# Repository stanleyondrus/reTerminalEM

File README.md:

# reTerminalEM

reTerminalEM is an open-source expansion module platform for reTerminal's high speed interface

#### More information: https://stanleyprojects.com/projects/reterminal_module/

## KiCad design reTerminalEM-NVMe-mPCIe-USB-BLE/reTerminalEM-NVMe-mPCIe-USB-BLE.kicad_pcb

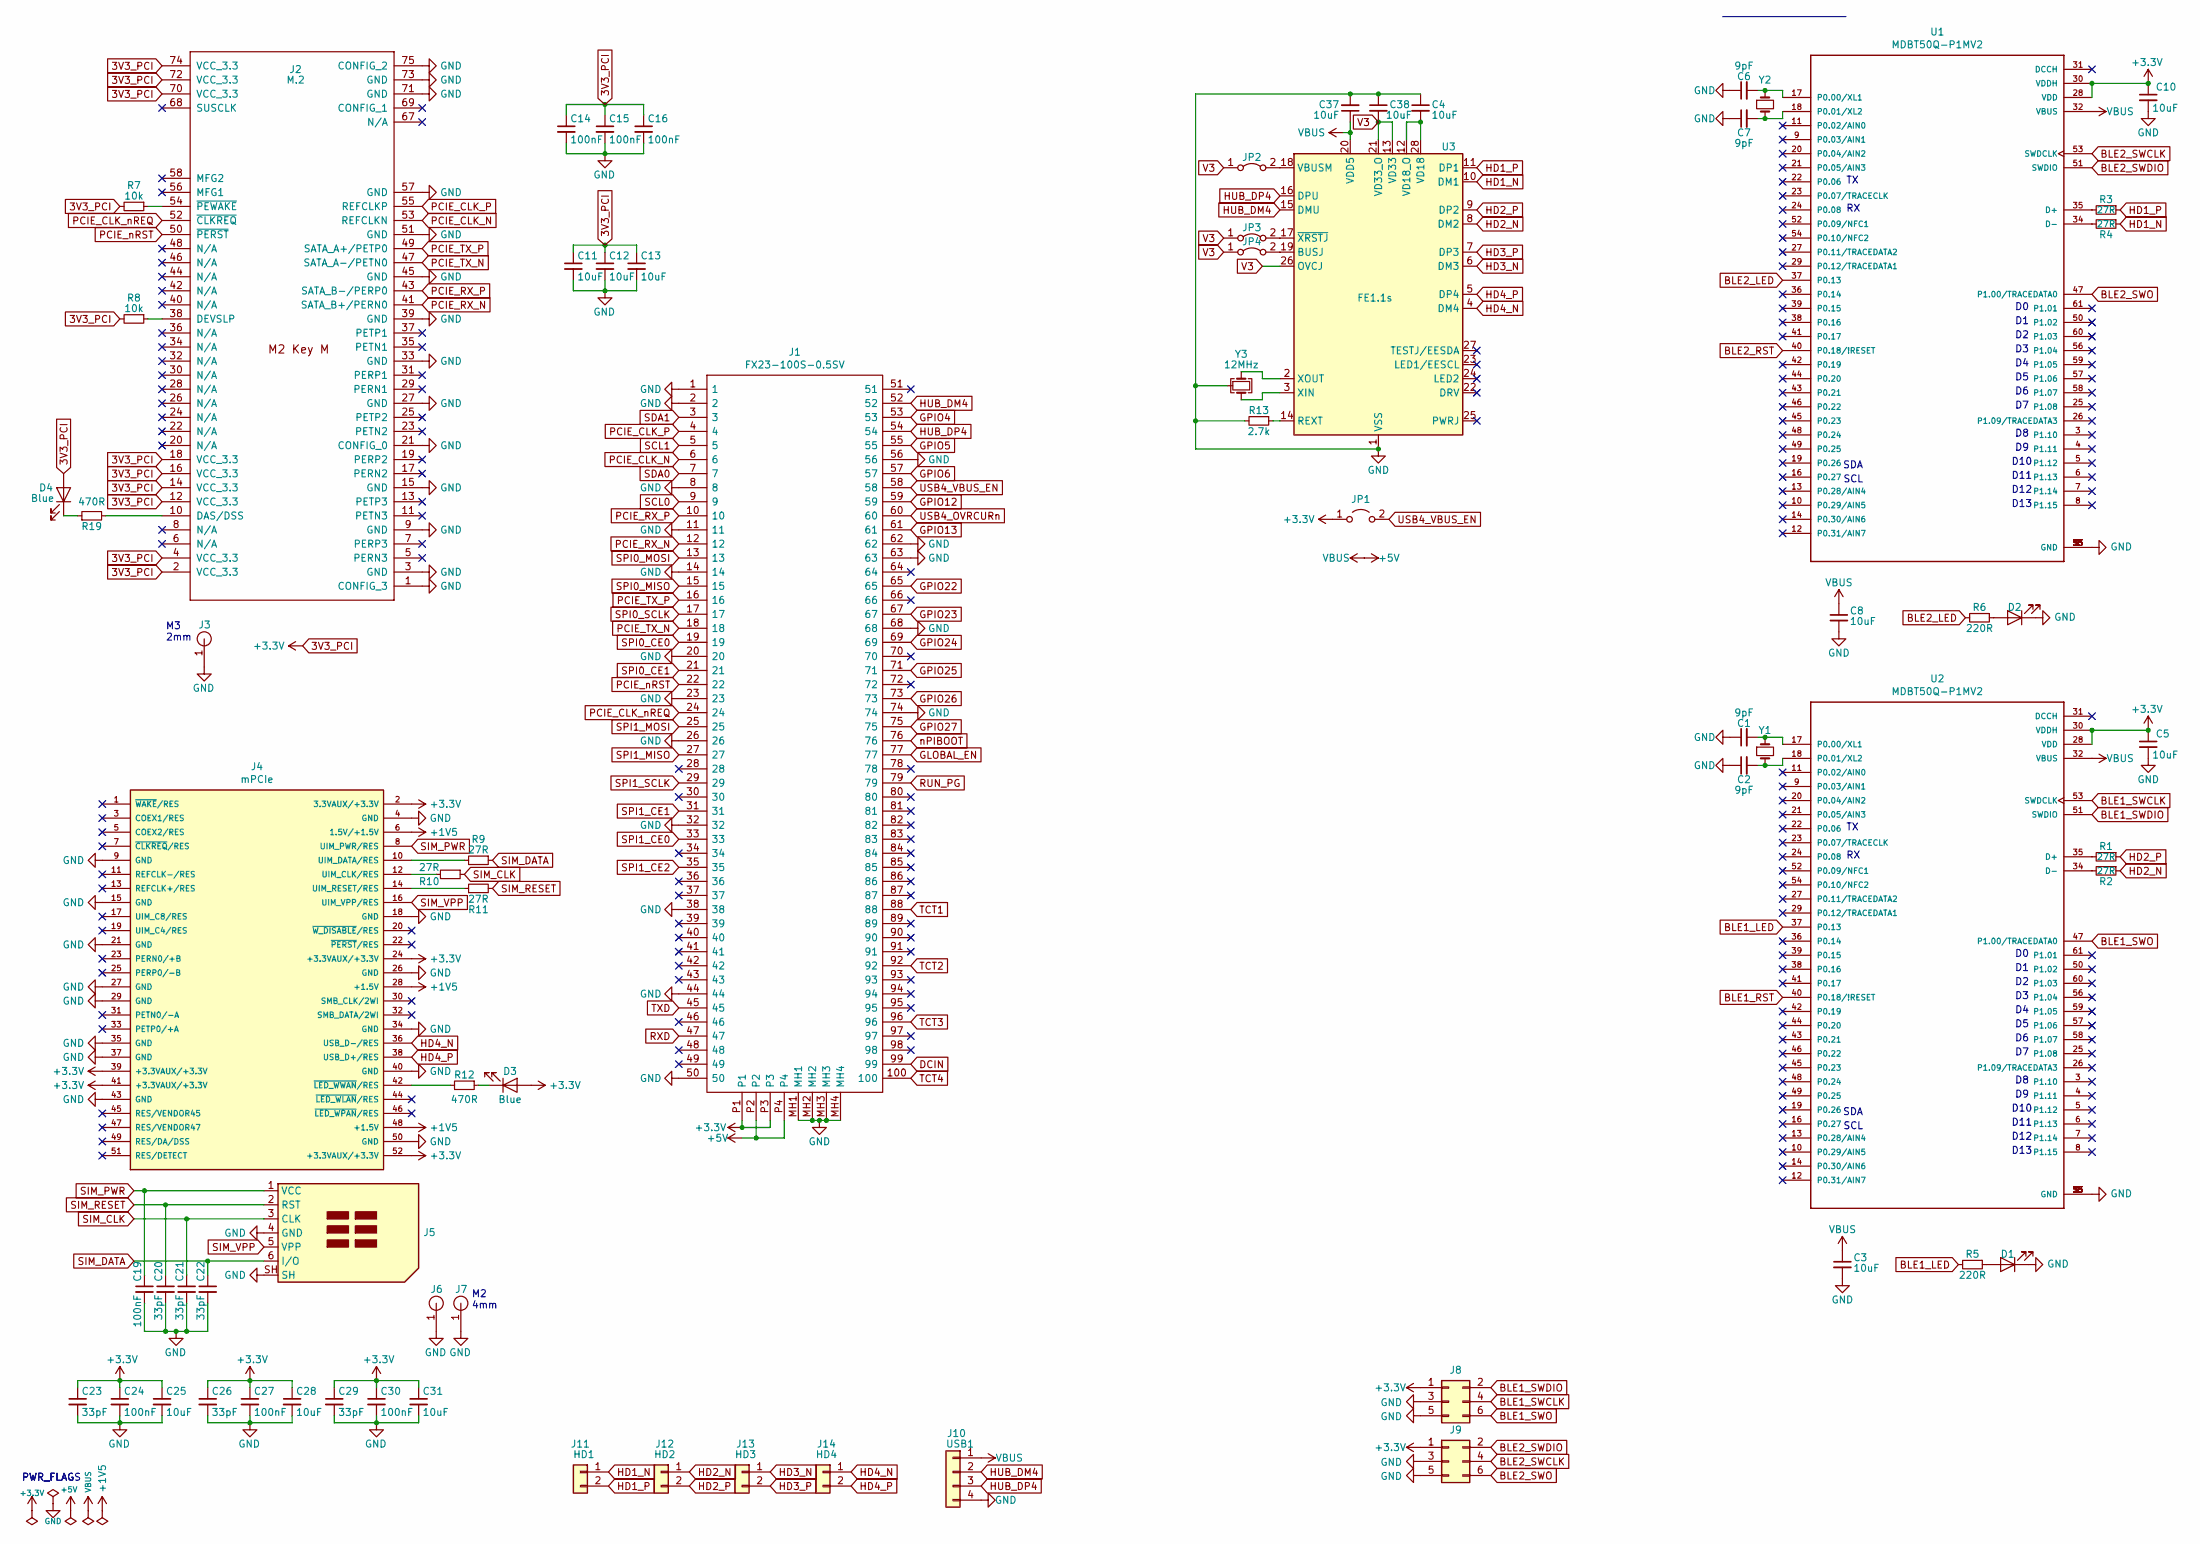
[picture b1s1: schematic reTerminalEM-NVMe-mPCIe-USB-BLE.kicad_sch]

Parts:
C1, C2, C6, C7: 9pF; C_0402_1005Metric; MPN CBR04C909B1GAC
C3, C5, C8, C10: 10uF; C_0402_1005Metric; MPN LDK105CBJ106MVLF
C4, C11, C12, C13, C25, C28, C31, C37, C38: 10uF; C_0805_2012Metric; MPN CL21A106KAYNNNE
C14, C15, C16, C19, C24, C27, C30: 100nF; C_0402_1005Metric; MPN CC0402KRX7R7BB104
C20, C21, C22, C23, C26, C29: 33pF; C_0402_1005Metric; MPN CC0402JRNPO9BN330
D1, D2: R; LED_0402_1005Metric; MPN NCD0402R1
D3, D4: Blue; LED_0402_1005Metric; MPN NCD0402B1
J1: FX23-100S-0.5SV; MPN FX23-100S-0.5SV
J2: M.2; TE_1-2199230-5; MPN 1-2199230-5
J3: J_Standoff_M3_H2.5; WE_WA-SMSI_9774025360; MPN 9774020360R
J4: mPCIe; TE_20412621; MPN 2041262-1
J5: J_SIM_Card_Nano_6P_Shielded; Molex_104224-0820; MPN 104224-0820
J6, J7: J_Standoff_M2_H4; WE_WA-SMSI_9774040243; MPN 9774040243R
J8, J9: Conn_02x03_Odd_Even; Tag-Connect_TC2030-IDC-NL_2x03_P1.27mm_Vertical
J10: USB1; PinSocket_1x04_P2.54mm_Vertical
J11: HD1; PinSocket_1x02_P2.54mm_Vertical
J12: HD2; PinSocket_1x02_P2.54mm_Vertical
J13: HD3; PinSocket_1x02_P2.54mm_Vertical
J14: HD4; PinSocket_1x02_P2.54mm_Vertical
JP1: Jumper_2_Open; SolderJumper-2_P1.3mm_Open_RoundedPad1.0x1.5mm
JP2, JP3, JP4: Jumper_2_Closed; SolderJumper-2_P1.3mm_Bridged_RoundedPad1.0x1.5mm
R1, R2, R3, R4, R9, R10, R11: 27R; R_0402_1005Metric; MPN RC0402JR-0727RL
R5, R6: 220R; R_0402_1005Metric; MPN 0402WGF2200TCE
R7, R8: 10k; R_0402_1005Metric; MPN RC0402FR-0710KL
R12, R19: 470R; R_0402_1005Metric; MPN RC0402FR-07470RL
R13: 2.7k; R_0402_1005Metric; MPN RC0402FR-072K7L
U1, U2: MDBT50Q-P1MV2; MPN MDBT50Q-P1MV2
U3: FE1.1s; SSOP-28_3.9x9.9mm_P0.635mm
Y1, Y2: 32.768kHz; Y_3215-2Pin_3.2x1.5mm; MPN FC-135 32.7680KA-AG3
Y3: 12MHz; Crystal_SMD_3225-4Pin_3.2x2.5mm; MPN 403WF12012IMR

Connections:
3V3_PCI: C5.1, C10.1, C11.1, C12.1, C13.1, C14.1, C15.1, C16.1, C23.1, C24.1, C25.1, C26.1, C27.1, C28.1, C29.1, C30.1, C31.1, D3.2 (A), D4.2 (A), J1.P1, J1.P3, J2.2 (VCC_3.3), J2.4 (VCC_3.3), J2.12 (VCC_3.3), J2.14 (VCC_3.3), J2.16 (VCC_3.3), J2.18 (VCC_3.3), J2.70 (VCC_3.3), J2.72 (VCC_3.3), J2.74 (VCC_3.3), J4.2 (3.3VAUX/+3.3V), J4.24 (+3.3VAUX/+3.3V), J4.39 (+3.3VAUX/+3.3V), J4.41 (+3.3VAUX/+3.3V), J4.52 (+3.3VAUX/+3.3V), J8.1, J9.1, JP1.1 (A), R7.2, R8.2, U1.28 (VDD), U1.30 (VDDH), U2.28 (VDD), U2.30 (VDDH)
+1V5: J4.6 (1.5V/+1.5V), J4.28 (+1.5V), J4.48 (+1.5V)
+5V: C3.1, C8.1, C37.1, J1.P2, J1.P4, J10.1, U1.32 (VBUS), U2.32 (VBUS), U3.20 (VDD5)
BLE1_LED: R5.2, U2.37 (P0.13)
BLE1_RST: U2.40 (P0.18/!RESET)
BLE1_SWCLK: J8.4, U2.53 (SWDCLK)
BLE1_SWDIO: J8.2, U2.51 (SWDIO)
BLE1_SWO: J8.6, U2.47 (P1.00/TRACEDATA0)
BLE2_LED: R6.2, U1.37 (P0.13)
BLE2_RST: U1.40 (P0.18/!RESET)
BLE2_SWCLK: J9.4, U1.53 (SWDCLK)
BLE2_SWDIO: J9.2, U1.51 (SWDIO)
BLE2_SWO: J9.6, U1.47 (P1.00/TRACEDATA0)
DCIN: J1.99
GLOBAL_EN: J1.77
GND: C1.1, C2.1, C3.2, C4.1, C5.2, C6.1, C7.1, C8.2, C10.2, C11.2, C12.2, C13.2, C14.2, C15.2, C16.2, C19.2, C20.2, C21.2, C22.2, C23.2, C24.2, C25.2, C26.2, C27.2, C28.2, C29.2, C30.2, C31.2, C37.2, C38.1, D1.1 (K), D2.1 (K), J1.1, J1.2, J1.8, J1.11, J1.14, J1.20, J1.23, J1.26, J1.32, J1.38, J1.44, J1.50, J1.56, J1.62, J1.63, J1.68, J1.74, J1.MH1, J1.MH2, J1.MH3, J1.MH4, J2.1 (CONFIG_3), J2.3 (GND), J2.9 (GND), J2.15 (GND), J2.21 (CONFIG_0), J2.27 (GND), J2.33 (GND), J2.39 (GND), J2.45 (GND), J2.51 (GND), J2.57 (GND), J2.71 (GND), J2.73 (GND), J2.75 (CONFIG_2), J2.S1 (GND), J2.S2 (GND), J3.1, J4.4 (GND), J4.9 (GND), J4.15 (GND), J4.18 (GND), J4.21 (GND), J4.26 (GND), J4.27 (GND), J4.29 (GND), J4.34 (GND), J4.35 (GND), J4.37 (GND), J4.40 (GND), J4.43 (GND), J4.50 (GND), J5.4 (GND), J5.SH, J6.1, J7.1, J8.3, J8.5, J9.3, J9.5, J10.4, R13.2, U1.1 (GND), U1.2 (GND), U1.15 (GND), U1.33 (GND), U1.55 (GND), U2.1 (GND), U2.2 (GND), U2.15 (GND), U2.33 (GND), U2.55 (GND), U3.1 (VSS), Y3.2, Y3.4
GPIO4: J1.53
GPIO5: J1.55
GPIO6: J1.57
GPIO12: J1.59
GPIO13: J1.61
GPIO22: J1.65
GPIO23: J1.67
GPIO24: J1.69
GPIO25: J1.71
GPIO26: J1.73
GPIO27: J1.75
HD1_N: J11.1, R4.1, U3.10 (DM1)
HD1_P: J11.2, R3.1, U3.11 (DP1)
HD2_N: J12.1, R2.1, U3.8 (DM2)
HD2_P: J12.2, R1.1, U3.9 (DP2)
HD3_N: J13.1, U3.6 (DM3)
HD3_P: J13.2, U3.7 (DP3)
HD4_N: J4.36 (USB_D-/RES), J14.1, U3.4 (DM4)
HD4_P: J4.38 (USB_D+/RES), J14.2, U3.5 (DP4)
HUB_DM4: J1.52, J10.2, U3.15 (DMU)
HUB_DP4: J1.54, J10.3, U3.16 (DPU)
unnamed: C1.2, U2.17 (P0.00/XL1), Y1.1
unnamed: C2.2, U2.18 (P0.01/XL2), Y1.2
unnamed: C4.2, U3.12 (VD18_O), U3.28 (VD18)
unnamed: C6.2, U1.17 (P0.00/XL1), Y2.1
unnamed: C7.2, U1.18 (P0.01/XL2), Y2.2
unnamed: D1.2 (A), R5.1
unnamed: D2.2 (A), R6.1
unnamed: D3.1 (K), R12.1
unnamed: D4.1 (K), R19.1
unnamed: J2.10 (DAS/DSS), R19.2
unnamed: J2.38 (DEVSLP), R8.1
unnamed: J2.54 (~PEWAKE), R7.1
unnamed: J4.10 (UIM_DATA/RES), R9.2
unnamed: J4.12 (UIM_CLK/RES), R10.2
unnamed: J4.14 (UIM_RESET/RES), R11.1
unnamed: J4.42 (~LED_WWAN/RES), R12.2
unnamed: JP2.2 (B), U3.18 (VBUSM)
unnamed: JP3.2 (B), U3.17 (~XRSTJ)
unnamed: JP4.2 (B), U3.19 (BUSJ)
unnamed: R1.2, U2.35 (D+)
unnamed: R2.2, U2.34 (D-)
unnamed: R3.2, U1.35 (D+)
unnamed: R4.2, U1.34 (D-)
unnamed: R13.1, U3.14 (REXT)
unnamed: U3.2 (XOUT), Y3.1
unnamed: U3.3 (XIN), Y3.3
PCIE_CLK_N: J1.6, J2.53 (REFCLKN)
PCIE_CLK_P: J1.4, J2.55 (REFCLKP)
PCIE_CLK_nREQ: J1.24, J2.52 (~CLKREQ)
PCIE_RX_N: J1.12, J2.41 (SATA_B+/PERN0)
PCIE_RX_P: J1.10, J2.43 (SATA_B-/PERP0)
PCIE_TX_N: J1.18, J2.47 (SATA_A-/PETN0)
PCIE_TX_P: J1.16, J2.49 (SATA_A+/PETP0)
PCIE_nRST: J1.22, J2.50 (~PERST)
RUN_PG: J1.79
RXD: J1.47
SCL0: J1.9
SCL1: J1.5
SDA0: J1.7
SDA1: J1.3
SIM_CLK: C21.1, J5.3 (CLK), R10.1
SIM_DATA: C22.1, J5.6 (I/O), R9.1
SIM_PWR: C19.1, J4.8 (UIM_PWR/RES), J5.1 (VCC)
SIM_RESET: C20.1, J5.2 (RST), R11.2
SIM_VPP: J4.16 (UIM_VPP/RES), J5.5 (VPP)
SPI0_CE0: J1.19
SPI0_CE1: J1.21
SPI0_MISO: J1.15
SPI0_MOSI: J1.13
SPI0_SCLK: J1.17
SPI1_CE0: J1.33
SPI1_CE1: J1.31
SPI1_CE2: J1.35
SPI1_MISO: J1.27
SPI1_MOSI: J1.25
SPI1_SCLK: J1.29
TCT1: J1.88
TCT2: J1.92
TCT3: J1.96
TCT4: J1.100
TXD: J1.45
USB4_OVRCURn: J1.60
USB4_VBUS_EN: J1.58, JP1.2 (B)
V3: C38.2, JP2.1 (A), JP3.1 (A), JP4.1 (A), U3.13 (VD33), U3.21 (VD33_O), U3.26 (OVCJ)
nPIBOOT: J1.76

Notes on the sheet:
SDA
SCL
D11
D12
D10
M3 2mm
D13
PWR_FLAG
M2 4mm
PWR_FLAGS

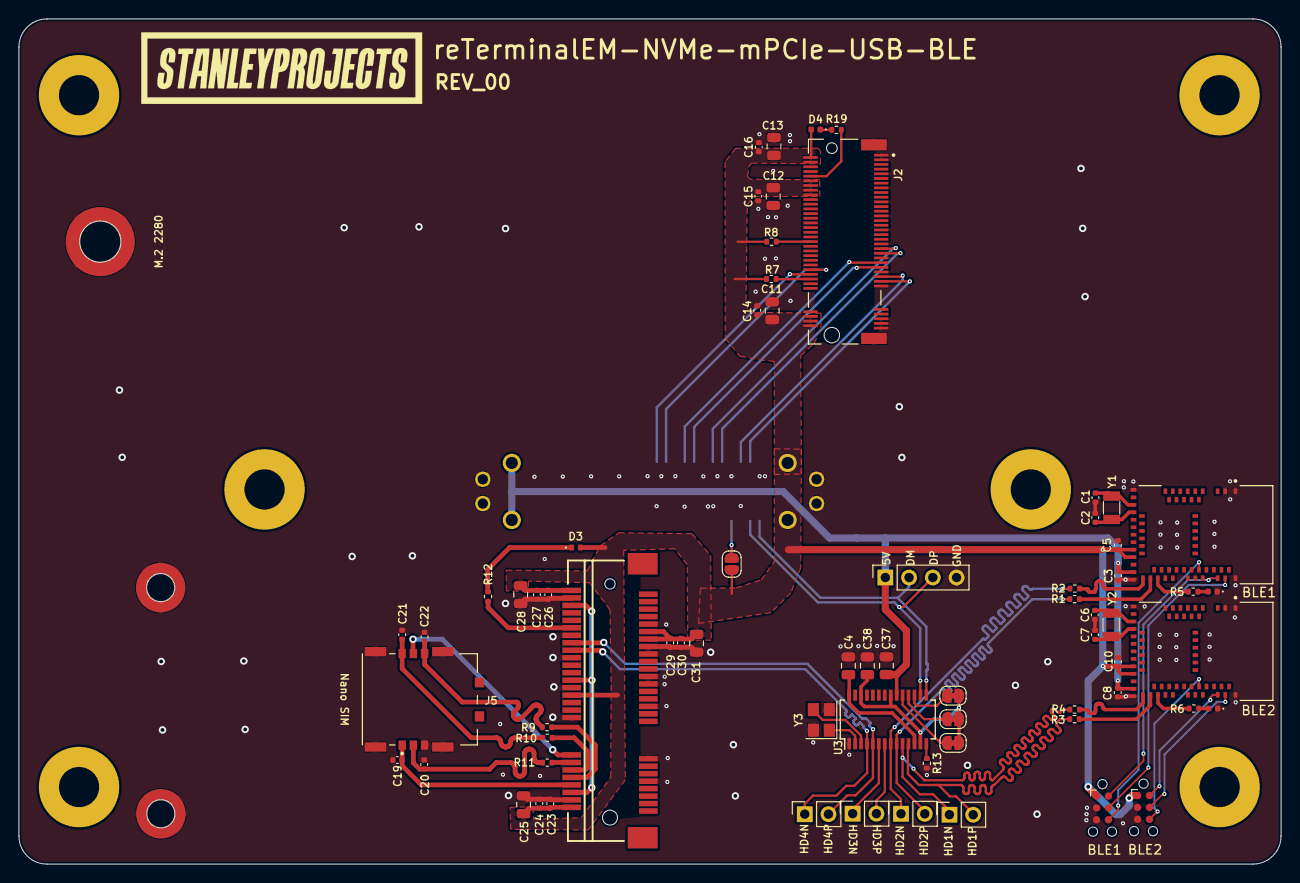
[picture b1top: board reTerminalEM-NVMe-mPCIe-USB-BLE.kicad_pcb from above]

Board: 2 copper layers, 135.0 x 90.4 mm, 72 parts (1 on the bottom side), 63 nets.

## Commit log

2021-11-23 init
2021-11-24 fixing dimensions, adding .step, .dxf, .pdf
2021-11-29 reTerminalEM-NVMe-mPCIe-USB
2022-06-23 no message
